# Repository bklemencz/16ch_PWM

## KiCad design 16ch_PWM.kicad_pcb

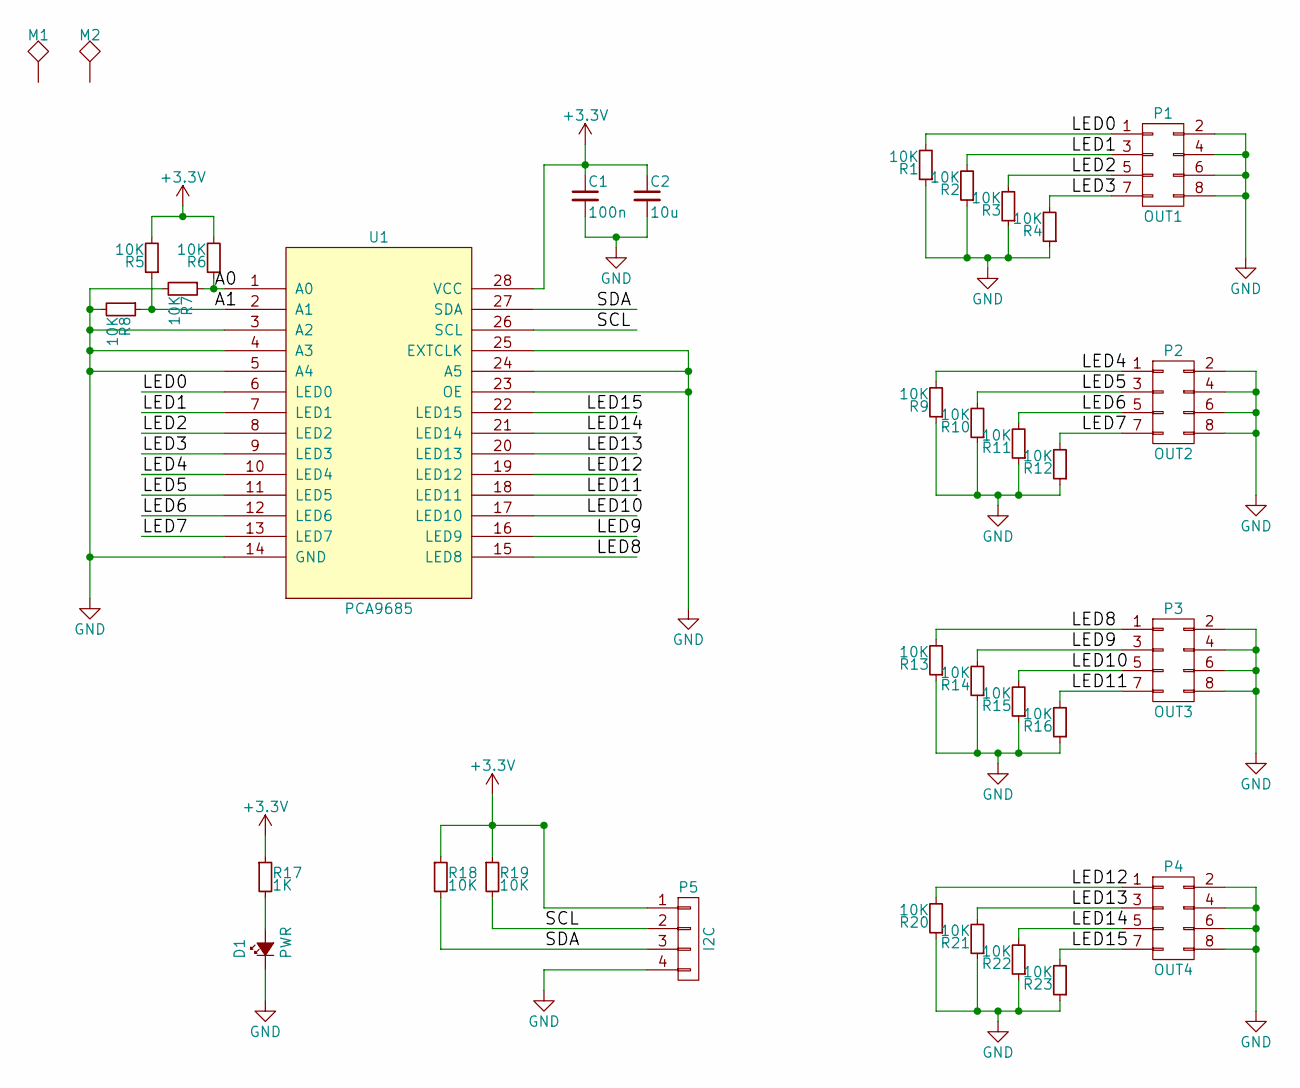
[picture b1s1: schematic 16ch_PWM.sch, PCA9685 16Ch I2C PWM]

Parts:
C1: 100n; C_0805
C2: 10u; C_1206
D1: PWR; LED_0805
M1, M2: TST; MountingHole_3.2mm_M3
P1: OUT1; Pin_Header_Straight_2x04_Pitch2.54mm
P2: OUT2; Pin_Header_Straight_2x04_Pitch2.54mm
P3: OUT3; Pin_Header_Straight_2x04_Pitch2.54mm
P4: OUT4; Pin_Header_Straight_2x04_Pitch2.54mm
P5: I2C; Pin_Header_Straight_1x04_Pitch2.54mm
R1, R2, R3, R4, R5, R6, R7, R8, R9, R10, R11, R12, R13, R14, R15, R16, R18, R19, R20, R21, R22, R23: 10K; R_0805
R17: 1K; R_0805
U1: PCA9685; TSSOP-28_4.4x9.7mm_Pitch0.65mm

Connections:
+3V3: C1.1, C2.1, P5.1, R5.2, R6.2, R17.1, R18.1, R19.1, U1.28 (VCC)
/A0: R6.1, R7.1, U1.1 (A0)
/A1: R5.1, R8.1, U1.2 (A1)
/LED0: P1.1, R1.2, U1.6 (LED0)
/LED1: P1.3, R2.2, U1.7 (LED1)
/LED2: P1.5, R3.2, U1.8 (LED2)
/LED3: P1.7, R4.2, U1.9 (LED3)
/LED4: P2.1, R9.2, U1.10 (LED4)
/LED5: P2.3, R10.2, U1.11 (LED5)
/LED6: P2.5, R11.2, U1.12 (LED6)
/LED7: P2.7, R12.2, U1.13 (LED7)
/LED8: P3.1, R13.2, U1.15 (LED8)
/LED9: P3.3, R14.2, U1.16 (LED9)
/LED10: P3.5, R15.2, U1.17 (LED10)
/LED11: P3.7, R16.2, U1.18 (LED11)
/LED12: P4.1, R20.2, U1.19 (LED12)
/LED13: P4.3, R21.2, U1.20 (LED13)
/LED14: P4.5, R22.2, U1.21 (LED14)
/LED15: P4.7, R23.2, U1.22 (LED15)
/SCL: P5.2, R19.2, U1.26 (SCL)
/SDA: P5.3, R18.2, U1.27 (SDA)
GND: C1.2, C2.2, D1.1 (K), P1.2, P1.4, P1.6, P1.8, P2.2, P2.4, P2.6, P2.8, P3.2, P3.4, P3.6, P3.8, P4.2, P4.4, P4.6, P4.8, P5.4, R1.1, R2.1, R3.1, R4.1, R7.2, R8.2, R9.1, R10.1, R11.1, R12.1, R13.1, R14.1, R15.1, R16.1, R20.1, R21.1, R22.1, R23.1, U1.3 (A2), U1.4 (A3), U1.5 (A4), U1.14 (GND), U1.23 (OE), U1.24 (A5), U1.25 (EXTCLK)
unnamed: D1.2 (A), R17.2

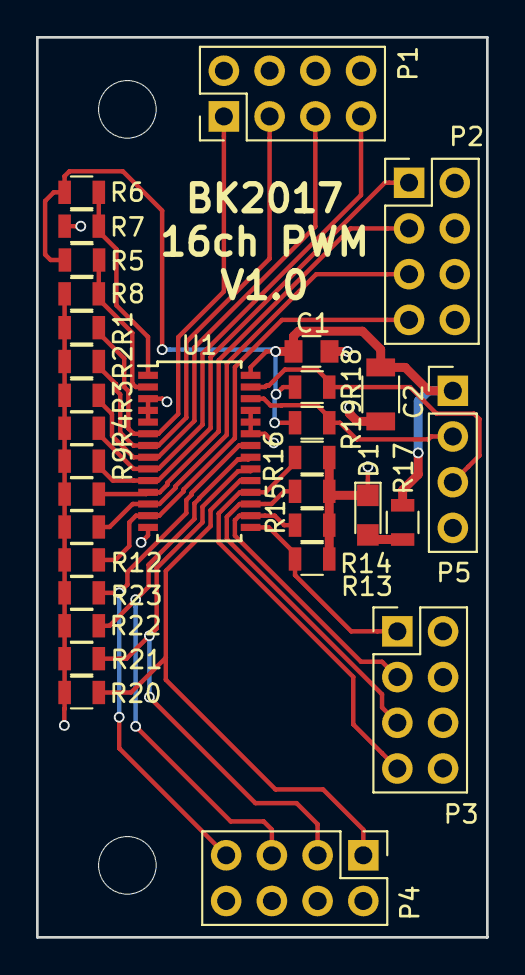
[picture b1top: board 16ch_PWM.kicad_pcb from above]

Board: 2 copper layers, 25.0 x 50.0 mm, 34 parts (0 on the bottom side), 23 nets.

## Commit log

2017-04-03 :space_invader: Added .gitattributes & .gitignore files
2017-04-03 Initial
2017-07-04 Gerber
